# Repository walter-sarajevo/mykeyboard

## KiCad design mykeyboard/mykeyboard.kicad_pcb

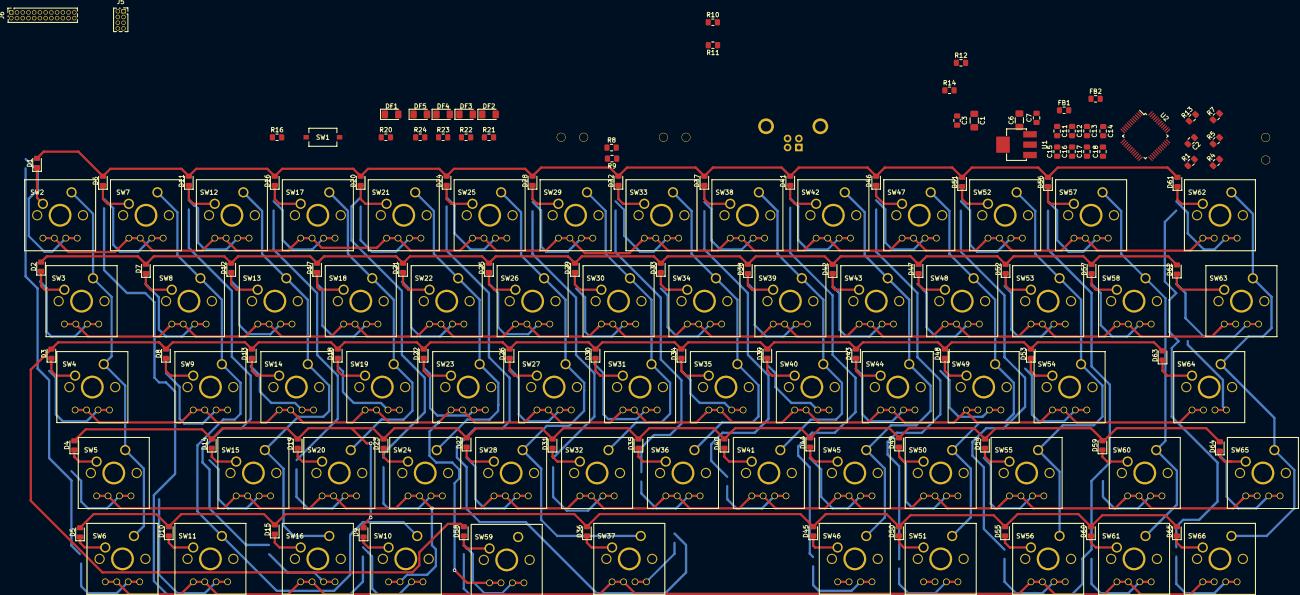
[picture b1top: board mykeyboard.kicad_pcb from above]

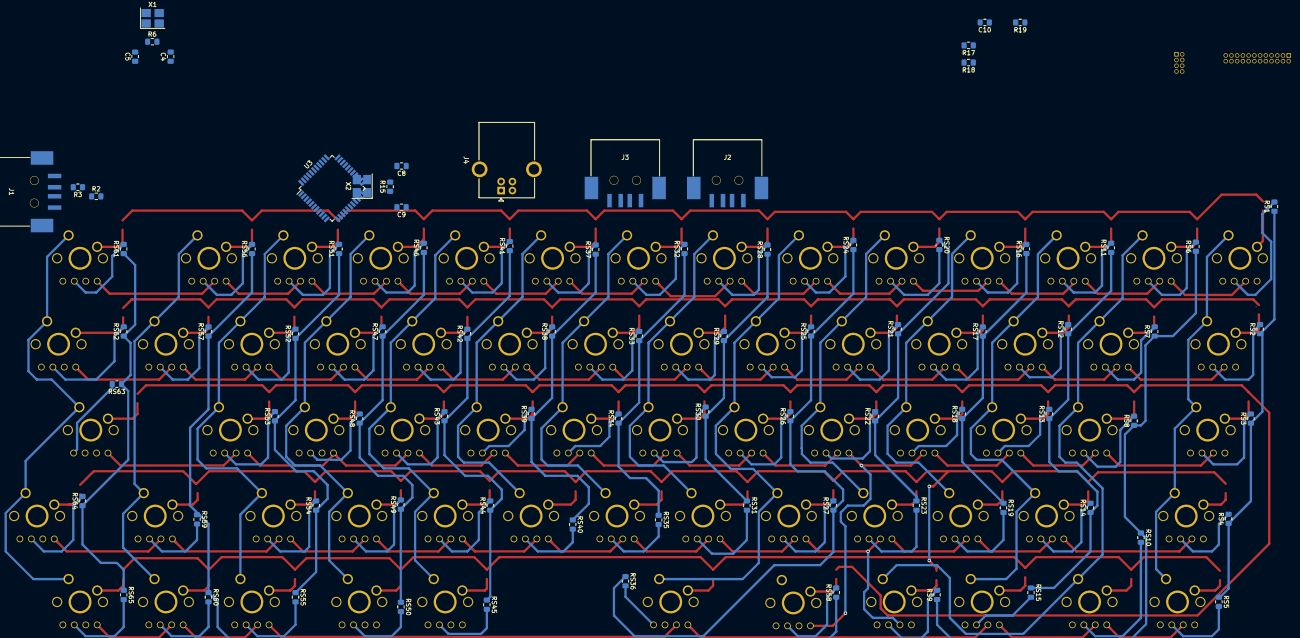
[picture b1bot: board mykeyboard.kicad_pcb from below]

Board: 2 copper layers, 256 parts (84 on the bottom side), 215 nets.

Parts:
C1, C6: 10u; C_1206_3216Metric_Pad1.42x1.75mm_HandSolder
C2, C3, C7, C10, C11, C12, C13, C14, C15, C16, C17, C18: 104; C_0805_2012Metric_Pad1.15x1.40mm_HandSolder
C4, C5, C8, C9: 22p; C_0805_2012Metric_Pad1.15x1.40mm_HandSolder
D1, D2, D3, D4, D5, D6, D7, D8, D9, D10, D11, D12, D13, D14, D15, D16, D17, D18, D19, D20, D21, D22, D23, D24, D25, D26, D27, D28, D29, D30, D31, D32, D33, D34, D35, D36, D37, D38, D39, D40, D41, D42, D43, D44, D45, D46, D47, D48, D49, D50, D51, D52, D53, D54, D55, D56, D57, D58, D59, D60, D61, D62, D63, D64, D65: D_ALT; D_0805_2012Metric_Pad1.15x1.40mm_HandSolder
DF1, DF2, DF3, DF4, DF5: 0603G; LED_1206_3216Metric_Pad1.42x1.75mm_HandSolder
FB1, FB2: L_0805_2012Metric_Pad1.15x1.40mm_HandSolder
J1, J2, J3: USB_A; USB-A
J4: USB_B; USB_B_OST_USB-B1HSxx_Horizontal
J5: Conn_01x08_Male; PinSocket_2x04_P1.27mm_Vertical
J6: Conn_01x24_Female; PinSocket_2x12_P1.27mm_Vertical
R1, R4, R5, R7: 100k; R_0805_2012Metric_Pad1.15x1.40mm_HandSolder
R2, R3, R8, R9, R10, R11, R12, R14, R16, R17, R18: 22; R_0805_2012Metric_Pad1.15x1.40mm_HandSolder
R6, R15: 1M; R_0805_2012Metric_Pad1.15x1.40mm_HandSolder
R13: 680; R_0805_2012Metric_Pad1.15x1.40mm_HandSolder
R19: 10k; R_0805_2012Metric_Pad1.15x1.40mm_HandSolder
R20: 300; R_0805_2012Metric_Pad1.15x1.40mm_HandSolder
R21, R22, R23, R24: 1k; R_0805_2012Metric_Pad1.15x1.40mm_HandSolder
RS1, RS2, RS3, RS4, RS5, RS6, RS7, RS8, RS9, RS10, RS11, RS12, RS13, RS14, RS15, RS16, RS17, RS18, RS19, RS20, RS21, RS22, RS23, RS24, RS25, RS26, RS27, RS28, RS29, RS30, RS31, RS32, RS33, RS34, RS35, RS36, RS37, RS38, RS39, RS40, RS41, RS42, RS43, RS44, RS45, RS46, RS47, RS48, RS49, RS50, RS51, RS52, RS53, RS54, RS55, RS56, RS57, RS58, RS59, RS60, RS61, RS62, RS63, RS64, RS65: 1k; R_0805_2012Metric_Pad1.15x1.40mm_HandSolder
SW1: SW_SPST; SW
SW2, SW3, SW4, SW5, SW6, SW7, SW8, SW9, SW10, SW11, SW12, SW13, SW14, SW15, SW16, SW17, SW18, SW19, SW20, SW21, SW22, SW23, SW24, SW25, SW26, SW27, SW28, SW29, SW30, SW31, SW32, SW33, SW34, SW35, SW36, SW37, SW38, SW39, SW40, SW41, SW42, SW43, SW44, SW45, SW46, SW47, SW48, SW49, SW50, SW51, SW52, SW53, SW54, SW55, SW56, SW57, SW58, SW59, SW60, SW61, SW62, SW63, SW64, SW65, SW66: KEY; MX_LED
U1: TLV1117-33; TLV1117-DCY
U2: GL850A; LQFP-48_7x7mm_P0.5mm
U3: ATmega32U4-AU; TQFP-44_10x10mm_P0.8mm
X1: 3325-12MHz; Crystal_SMD_3225-4Pin_3.2x2.5mm_HandSoldering
X2: 3325-16MHz; Crystal_SMD_3225-4Pin_3.2x2.5mm_HandSoldering

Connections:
/DM0: R12.1, U2.3
/DM1: R17.2, U2.5
/DM2: R3.1, U2.9
/DM3: R9.1, U2.18
/DM4: R11.1, U2.22
/DP0: R14.2, U2.4
/DP1: R18.2, U2.6
/DP2: R2.2, U2.10
/DP3: R8.2, U2.19
/DP4: R10.2, U2.23
/GPIO0: J6.21, R21.1, U3.36
/GPIO1: J6.22, R22.1, U3.37
/GPIO2: J6.23, R23.1, U3.38
/GPIO3: J6.24, R24.1, U3.39
/RESET1#: C2.1, R1.2, U2.28
/RESET2#: J5.7, R16.2, SW1.1, U3.13
AVCC: C11.1, C12.1, C13.1, C14.1, FB1.1, U2.1, U2.7, U2.12, U2.16, U2.20
DGND: C2.2, C4.1, C5.1, C6.2, C7.2, C15.2, C16.2, C17.2, C18.2, FB2.2, R7.2, U1.1, U2.26, U2.33, U2.38, U2.43, U2.47
DVCC: C6.1, C7.1, C15.1, C16.1, C17.1, C18.1, FB1.2, R1.1, R4.2, R5.2, U1.2, U2.27, U2.34, U2.39, U2.44
GND: C1.2, C3.2, C8.1, C9.1, C10.2, C11.2, C12.2, C13.2, C14.2, FB2.1, J1.4, J2.4, J3.4, J4.4, J5.8, R13.2, R19.2, SW1.2, U2.2, U2.8, U2.13, U2.17, U2.21, U3.5, U3.15, U3.23, U3.35, U3.43
unnamed: C4.2, R6.2, U2.15, X1.3
unnamed: C5.2, R6.1, U2.14, X1.1
unnamed: C8.2, R15.2, U3.16, X2.3
unnamed: C9.2, R15.1, U3.17, X2.1
unnamed: C10.1, U3.6
unnamed: D1.1, SW2.2
unnamed: D2.1, SW3.2
unnamed: D3.1, SW4.2
unnamed: D4.1, SW5.2
unnamed: D5.1, SW6.2
unnamed: D6.1, SW7.2
unnamed: D7.1, SW8.2
unnamed: D8.1, SW9.2
unnamed: D9.1, SW10.2
unnamed: D10.1, SW11.2
unnamed: D11.1, SW12.2
unnamed: D12.1, SW13.2
unnamed: D13.1, SW14.2
unnamed: D14.1, SW15.2
unnamed: D15.1, SW16.2
unnamed: D16.1, SW17.2
unnamed: D17.1, SW18.2
unnamed: D18.1, SW19.2
unnamed: D19.1, SW20.2
unnamed: D20.1, SW21.2
unnamed: D21.1, SW22.2
unnamed: D22.1, SW23.2
unnamed: D23.1, SW24.2
unnamed: D24.1, SW25.2
unnamed: D25.1, SW26.2
unnamed: D26.1, SW27.2
unnamed: D27.1, SW28.2
unnamed: D28.1, SW29.2
unnamed: D29.1, SW30.2
unnamed: D30.1, SW31.2
unnamed: D31.1, SW32.2
unnamed: D32.1, SW33.2
unnamed: D33.1, SW34.2
unnamed: D34.1, SW35.2
unnamed: D35.1, SW36.2
unnamed: D36.1, SW37.2
unnamed: D37.1, SW38.2
unnamed: D38.1, SW39.2
unnamed: D39.1, SW40.2
unnamed: D40.1, SW41.2
unnamed: D41.1, SW42.2
unnamed: D42.1, SW43.2
unnamed: D43.1, SW44.2
unnamed: D44.1, SW45.2
unnamed: D45.1, SW46.2
unnamed: D46.1, SW47.2
unnamed: D47.1, SW48.2
unnamed: D48.1, SW49.2
unnamed: D49.1, SW50.2
unnamed: D50.1, SW51.2
unnamed: D51.1, SW52.2
unnamed: D52.1, SW53.2
unnamed: D53.1, SW54.2
unnamed: D54.1, SW55.2
unnamed: D55.1, SW56.2
unnamed: D56.1, SW57.2
unnamed: D57.1, SW58.2
unnamed: D58.1, SW59.2
unnamed: D59.1, SW60.2
unnamed: D60.1, SW61.2
unnamed: D61.1, SW62.2
unnamed: D62.1, SW63.2
unnamed: D63.1, SW64.2
unnamed: D64.1, SW65.2
unnamed: D65.1, SW66.2
unnamed: DF1.1, R20.2
unnamed: DF2.1, R21.2
unnamed: DF3.1, R22.2
unnamed: DF4.1, R23.2
unnamed: DF5.1, R24.2
unnamed: J1.2, R3.2
unnamed: J1.3, R2.1
unnamed: J2.2, R9.2
unnamed: J2.3, R8.1
unnamed: J3.2, R11.2
unnamed: J3.3, R10.1
unnamed: J4.2, R12.2
unnamed: J4.3, R14.1
unnamed: R4.1, U2.40
unnamed: R5.1, U2.41
unnamed: R7.1, U2.37
unnamed: R13.1, U2.11
unnamed: R17.1, U3.4
unnamed: R18.1, U3.3
unnamed: R19.1, U3.33
unnamed: RS1.2, SW2.4
unnamed: RS2.2, SW3.4
unnamed: RS3.2, SW4.4
unnamed: RS4.2, SW5.4
unnamed: RS5.2, SW6.4
unnamed: RS6.2, SW7.4
unnamed: RS7.2, SW8.4
unnamed: RS8.2, SW9.4
unnamed: RS9.2, SW10.4
unnamed: RS10.2, SW11.4
unnamed: RS11.2, SW12.4
unnamed: RS12.2, SW13.4
unnamed: RS13.2, SW14.4
unnamed: RS14.2, SW15.4
unnamed: RS15.2, SW16.4
unnamed: RS16.2, SW17.4
unnamed: RS17.2, SW18.4
unnamed: RS18.2, SW19.4
unnamed: RS19.2, SW20.4
unnamed: RS20.2, SW21.4
unnamed: RS21.2, SW22.4
unnamed: RS22.2, SW23.4
unnamed: RS23.2, SW24.4
unnamed: RS24.2, SW25.4
unnamed: RS25.2, SW26.4
unnamed: RS26.2, SW27.4
unnamed: RS27.2, SW28.4
unnamed: RS28.2, SW29.4
unnamed: RS29.2, SW30.4
unnamed: RS30.2, SW31.4
unnamed: RS31.2, SW32.4
unnamed: RS32.2, SW33.4
unnamed: RS33.2, SW34.4
unnamed: RS34.2, SW35.4
unnamed: RS35.2, SW36.4
unnamed: RS36.2, SW37.4
unnamed: RS37.2, SW38.4
unnamed: RS38.2, SW39.4
unnamed: RS39.2, SW40.4
unnamed: RS40.2, SW41.4
unnamed: RS41.2, SW42.4
unnamed: RS42.2, SW43.4
unnamed: RS43.2, SW44.4
unnamed: RS44.2, SW45.4
unnamed: RS45.2, SW46.4
unnamed: RS46.2, SW47.4
unnamed: RS47.2, SW48.4
unnamed: RS48.2, SW49.4
unnamed: RS49.2, SW50.4
unnamed: RS50.2, SW51.4
unnamed: RS51.2, SW52.4
unnamed: RS52.2, SW53.4
unnamed: RS53.2, SW54.4
unnamed: RS54.2, SW55.4
unnamed: RS55.2, SW56.4
unnamed: RS56.2, SW57.4
unnamed: RS57.2, SW58.4
unnamed: RS58.2, SW59.4
unnamed: RS59.2, SW60.4
unnamed: RS60.2, SW61.4
unnamed: RS61.2, SW62.4
unnamed: RS62.2, SW63.4
unnamed: RS63.2, SW64.4
unnamed: RS64.2, SW65.4
unnamed: RS65.2, SW66.4
VCC: C1.1, C3.1, DF1.2, DF2.2, DF3.2, DF4.2, DF5.2, J1.1, J2.1, J3.1, J4.1, J5.2, R16.1, U1.3, U3.2, U3.7, U3.14, U3.24, U3.34, U3.44
caps_led: J5.4, R20.1, U3.10
col1: SW2.1, SW3.1, SW4.1, SW5.1, SW6.1, U3.41
col2: SW7.1, SW8.1, SW9.1, SW10.1, SW11.1, U3.40
col3: SW12.1, SW13.1, SW14.1, SW15.1, SW16.1, U3.1
col4: SW17.1, SW18.1, SW19.1, SW20.1
col5: SW21.1, SW22.1, SW23.1, SW24.1
col6: SW25.1, SW26.1, SW27.1, SW28.1, SW37.1, U3.30
col7: SW29.1, SW30.1, SW31.1, SW32.1, U3.25
col8: J5.1, SW33.1, SW34.1, SW35.1, SW36.1, U3.9
col9: SW38.1, SW39.1, SW40.1, SW41.1, U3.12
col10: SW42.1, SW43.1, SW44.1, SW45.1, SW46.1, U3.29
col11: SW47.1, SW48.1, SW49.1, SW50.1, SW51.1, U3.28
col12: SW52.1, SW53.1, SW54.1, SW55.1, SW56.1, U3.27
col13: SW57.1, SW58.1, SW59.1, SW60.1, SW61.1, U3.26
col14: J5.3, SW62.1, SW63.1, SW64.1, SW65.1, SW66.1, U3.11, U3.32
lcol1: J6.6, RS1.1, RS2.1, RS3.1, RS4.1, RS5.1
lcol2: J6.7, RS6.1, RS7.1, RS8.1, RS9.1, RS10.1
lcol3: J6.8, RS11.1, RS12.1, RS13.1, RS14.1, RS15.1
lcol4: J6.9, RS16.1, RS17.1, RS18.1, RS19.1
lcol5: J6.10, RS20.1, RS21.1, RS22.1, RS23.1
lcol6: J6.11, RS24.1, RS25.1, RS26.1, RS27.1, RS36.1
lcol7: J6.12, RS28.1, RS29.1, RS30.1, RS31.1
lcol8: J6.13, RS32.1, RS33.1, RS34.1, RS35.1
lcol9: J6.14, RS37.1, RS38.1, RS39.1, RS40.1
lcol10: J6.15, RS41.1, RS42.1, RS43.1, RS44.1, RS45.1
lcol11: J6.16, RS46.1, RS47.1, RS48.1, RS49.1, RS50.1
lcol12: J6.17, RS51.1, RS52.1, RS53.1, RS54.1, RS55.1
lcol13: J6.18, RS56.1, RS57.1, RS58.1, RS59.1, RS60.1
lcol14: J6.19, RS61.1, RS62.1, RS63.1, RS64.1, RS65.1
lrow1: J6.1, SW2.3, SW7.3, SW12.3, SW17.3, SW21.3, SW25.3, SW29.3, SW33.3, SW38.3, SW42.3, SW47.3, SW52.3, SW57.3, SW62.3
lrow2: J6.2, SW3.3, SW8.3, SW13.3, SW18.3, SW22.3, SW26.3, SW30.3, SW34.3, SW39.3, SW43.3, SW48.3, SW53.3, SW58.3, SW63.3
lrow3: J6.3, SW4.3, SW9.3, SW14.3, SW19.3, SW23.3, SW27.3, SW31.3, SW35.3, SW40.3, SW44.3, SW49.3, SW54.3, SW59.3, SW64.3
lrow4: J6.4, SW5.3, SW10.3, SW15.3, SW20.3, SW24.3, SW28.3, SW32.3, SW36.3, SW41.3, SW45.3, SW50.3, SW55.3, SW60.3, SW65.3
lrow5: J6.5, SW6.3, SW11.3, SW16.3, SW37.3, SW56.3, SW61.3, SW66.3
row1: D1.2, D6.2, D11.2, D16.2, D20.2, D24.2, D28.2, D32.2, D37.2, D41.2, D46.2, D51.2, D56.2, D61.2, U3.18
row2: D2.2, D7.2, D12.2, D17.2, D21.2, D25.2, D29.2, D33.2, D38.2, D42.2, D47.2, D52.2, D57.2, D62.2, U3.19
row3: D3.2, D8.2, D13.2, D18.2, D22.2, D26.2, D30.2, D34.2, D39.2, D43.2, D48.2, D53.2, D58.2, D63.2, U3.20
row4: D4.2, D9.2, D14.2, D19.2, D23.2, D27.2, D31.2, D35.2, D40.2, D44.2, D49.2, D54.2, D59.2, D64.2, U3.21
row5: D5.2, D10.2, D15.2, D36.2, D45.2, D50.2, D55.2, D60.2, D65.2, U3.22

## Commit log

2018-11-12 the start of this missing
2018-11-12 try to select PATH
2018-11-12 1112,gogogo
2018-11-12 1112work
2018-11-12 complete matrix
2018-11-13 gogogogit pull!
2018-11-13 GOGOGOGOgit status!
2018-11-13 add a wrong check method.
2018-11-14 junk,but still a good prove.
